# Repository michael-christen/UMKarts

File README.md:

UMKarts
=======

A repository of code for the control of rc cars that can play Mario Kart.

Steps to get it running after a clone
1) Open up the gc libero project
2) Generate Components!! This is important. Laser Tag will not work without this
3) Program the device
4) Write Application Code
5) When you are asked for your workspace, switch it to (gc\SoftConsole\gc_MSS_MSS_CM3_0\)
6) Import the projects (I don't know why you have to do this, its annoying)
	Goto File->Import
	Under General select Existing Projects into Workspace
	Under Browse goto gc\SoftConsole\gc_MSS_MSS_CM3_0
	Select all and click Finish
	* Note: You should be able to just say Browse->Ok->Finish
7) The first time you'll have to setup your Debug Configuration

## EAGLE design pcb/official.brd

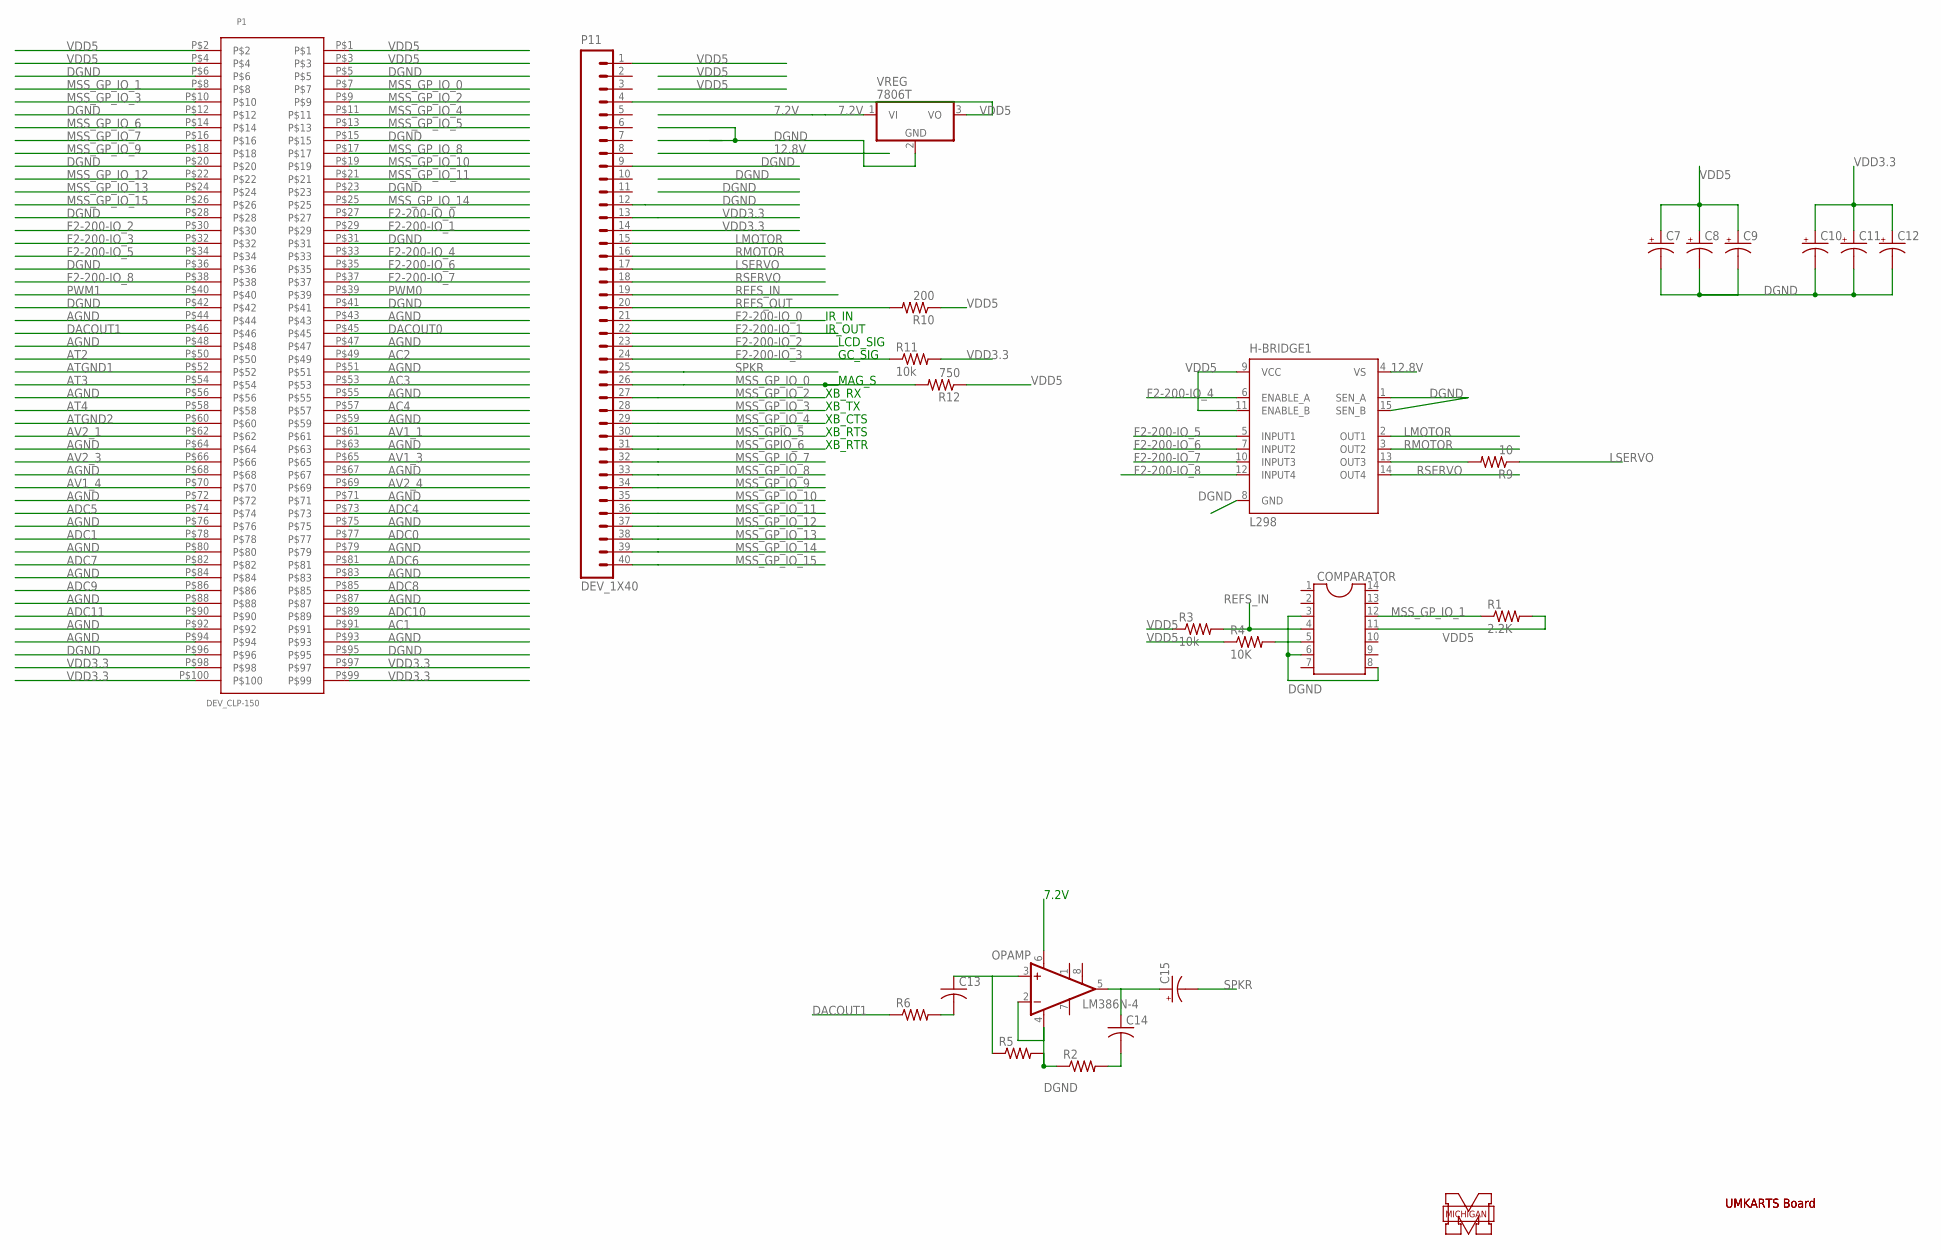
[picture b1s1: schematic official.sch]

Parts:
C7, C8, C9, C10, C11, C12, C15: CPOL-USB45181B; B45181B
C13: C-US075-032X103; C075-032X103
C14: C-US025-025X050; C025-025X050
COMPARATOR: DIL14S; SOCKET-14
H-BRIDGE1: L298; MULTIWATT-15
OPAMP: LM386N-4; DIL08
P1: DEV_CLP-150; CLP-150
P11: DEV_1X40; 1X40
R1: 2.2K; 0207/12
R2, R5, R6: R-US_0207/12; 0207/12
R3, R11: 10k; 0309/12
R4: 10K; 0309/12
R9: 10; 0309/12
R10: 200; 0309/12
R12: 750; 0309/12
VREG: 7806T; TO220H

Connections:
7.2V: P11.5, VREG.1 (VI)
12.8V: H-BRIDGE1.4 (VS), P11.8
AC1: P1.P$91
AC2: P1.P$49
AC3: P1.P$53
AC4: P1.P$57
ADC0: P1.P$77
ADC1: P1.P$78
ADC4: P1.P$73
ADC5: P1.P$74
ADC6: P1.P$81
ADC7: P1.P$82
ADC8: P1.P$85
ADC9: P1.P$86
ADC10: P1.P$89
ADC11: P1.P$90
AGND: P1.P$43, P1.P$44, P1.P$47, P1.P$48, P1.P$51, P1.P$55, P1.P$56, P1.P$59, P1.P$63, P1.P$64, P1.P$67, P1.P$68, P1.P$71, P1.P$72, P1.P$75, P1.P$76, P1.P$79, P1.P$80, P1.P$83, P1.P$84, P1.P$87, P1.P$88, P1.P$92, P1.P$93, P1.P$94
AT2: P1.P$50
AT3: P1.P$54
AT4: P1.P$58
ATGND1: P1.P$52
ATGND2: P1.P$60
AV1_1: P1.P$61
AV1_3: P1.P$65
AV1_4: P1.P$70
AV2_1: P1.P$62
AV2_3: P1.P$66
AV2_4: P1.P$69
DACOUT0: P1.P$45
DACOUT1: P1.P$46, R6.1
DGND: C7.-, C8.-, C9.-, C10.-, C11.-, C12.-, COMPARATOR.3, COMPARATOR.6, COMPARATOR.8, H-BRIDGE1.1 (SEN_A), H-BRIDGE1.8 (GND), H-BRIDGE1.15 (SEN_B), OPAMP.2 (-IN), OPAMP.4 (GND), P1.P$5, P1.P$6, P1.P$12, P1.P$15, P1.P$20, P1.P$23, P1.P$28, P1.P$31, P1.P$36, P1.P$41, P1.P$42, P1.P$95, P1.P$96, P11.6, P11.7, P11.9, P11.10, P11.11, P11.12, R2.1, R5.2, VREG.2 (GND); also elsewhere on the board
F2-200-IO_0: P1.P$27, P11.21
F2-200-IO_1: P1.P$29, P11.22
F2-200-IO_2: P1.P$30, P11.23
F2-200-IO_3: P1.P$32, P11.24, R11.1
F2-200-IO_4: H-BRIDGE1.6 (ENABLE_A), P1.P$33
F2-200-IO_5: H-BRIDGE1.5 (INPUT1), P1.P$34
F2-200-IO_6: H-BRIDGE1.7 (INPUT2), P1.P$35
F2-200-IO_7: H-BRIDGE1.10 (INPUT3), P1.P$37
F2-200-IO_8: H-BRIDGE1.12 (INPUT4), P1.P$38
LMOTOR: H-BRIDGE1.2 (OUT1), P11.15
LSERVO: P11.17, R9.1
MSS_GPIO_5: P11.30
MSS_GPIO_6: P11.31
MSS_GP_IO_0: P1.P$7, P11.26, R12.2
MSS_GP_IO_1: COMPARATOR.12, P1.P$8, R1.1
MSS_GP_IO_2: P1.P$9, P11.27
MSS_GP_IO_3: P1.P$10, P11.28
MSS_GP_IO_4: P1.P$11, P11.29
MSS_GP_IO_5: P1.P$13
MSS_GP_IO_6: P1.P$14
MSS_GP_IO_7: P1.P$16, P11.32
MSS_GP_IO_8: P1.P$17, P11.33
MSS_GP_IO_9: P1.P$18, P11.34
MSS_GP_IO_10: P1.P$19, P11.35
MSS_GP_IO_11: P1.P$21, P11.36
MSS_GP_IO_12: P1.P$22, P11.37
MSS_GP_IO_13: P1.P$24, P11.38
MSS_GP_IO_14: P1.P$25, P11.39
MSS_GP_IO_15: P1.P$26, P11.40
unnamed: H-BRIDGE1.13 (OUT3), R9.2
unnamed: C13.1, OPAMP.3 (+IN), R5.1
unnamed 63: COMPARATOR.5, R4.2; also elsewhere on the board
unnamed: C14.2, R2.2
unnamed: C14.1, C15.+, OPAMP.5 (OUT)
unnamed: C13.2, R6.2
PWM0: P1.P$39
PWM1: P1.P$40
REFS_IN: COMPARATOR.4, P11.19, R3.2
REFS_OUT: P11.20, R10.2
RMOTOR: H-BRIDGE1.3 (OUT2), P11.16
RSERVO: H-BRIDGE1.14 (OUT4), P11.18
SPKR: C15.-, P11.25
VDD3.3: C10.+, C11.+, C12.+, P1.P$97, P1.P$98, P1.P$99, P1.P$100, P11.13, P11.14, R11.2
VDD5: C7.+, C8.+, C9.+, COMPARATOR.11, H-BRIDGE1.9 (VCC), H-BRIDGE1.11 (ENABLE_B), P1.P$1, P1.P$2, P1.P$3, P1.P$4, P11.1, P11.2, P11.3, P11.4, R1.2, R3.1, R4.1, R10.1, R12.1, VREG.3 (VO)

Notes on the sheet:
MICHIGAN
7.2V
UMKARTS Board
XB_CTS
XB_RX
XB_TX
XB_RTS
XB_RTR
LCD_SIG
GC_SIG
IR_IN
IR_OUT
MAG_S

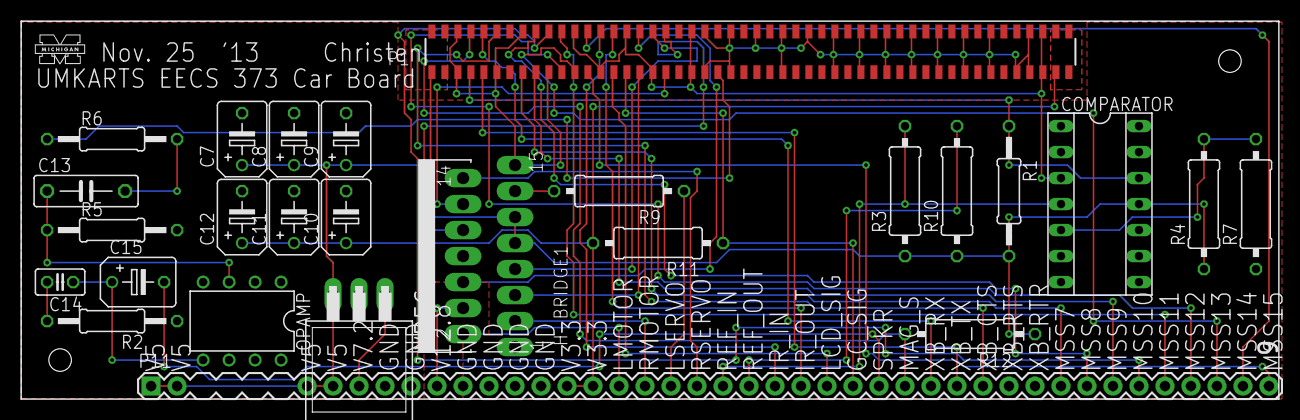
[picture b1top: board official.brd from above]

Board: 2 copper layers, 122.9 x 36.9 mm, 27 parts (0 on the bottom side), 43 nets.

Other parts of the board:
R7: 2.2k; 0309/12
U$1: UMICH

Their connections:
DGND: R7.1; also elsewhere on the board
unnamed 63: R7.2; also elsewhere on the board

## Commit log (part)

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2013-11-05 Bunch of initial files, your welcome
2013-11-05 wavebird
2013-11-06 Generalized query, and working on c lib
2013-11-07 branching gc control work
2013-11-07 Got general query working on pin J20
2013-11-12 Integrated driving
2013-11-12 Added controller files
2013-11-12 wavebirds hopefully working now, more testing needed
2013-11-12 fixed controller c code and moved back to controller.h/.c
2013-11-12 Adding intial code for our xbee driver
2013-11-12 Adding xbee receiving code. Not yet complete
2013-11-12 Added lcd interface
2013-11-14 Fixed slight bug in motor control
2013-11-14 Freed up UART1, fixed default controller data
2013-11-14 Started work on item code, NOT TESTED YET
2013-11-14 Adding UARTapb module drivers
2013-11-14 Fixed item stuff
2013-11-14 Moved variable defs out of header
2013-11-18 Adding library for circular buffer
    This library allows the instantion of a multiple producer single
    consumer buffer. This means that you can write to it in interrupts
    and there won't be any issues. We still maintain ordering.
2013-11-18 Adding .gitignore file to ignore vim .swp files
2013-11-18 Fixing bug where forgot to set item to NULL after it's been read
2013-11-18 Got item pickup working
2013-11-19 Adding xbee_writer.c class.
    xbee_writer always you to, byte by byte, generate a serial stream of
    xbee API 2 mode data from a packet in a cross platform way
2013-11-19 Changing API of circular buffer to be less confusing
    The circular buffer returned a value by passing a pointer to a
    pointer, which was just confusing to use. Now the read command
    returns a pointer to a data item to make it easier to use.
2013-11-19 Small change to hopefully prevent future bugs
2013-11-19 Adding interface files to make it easier to view which files to modify when tracking down a bug
2013-11-19 Modifying xbee_writer to make const correct
2013-11-19 Adding xbee_reader library for streaming xbee messages
    Adds the ability to read an xbee packet stream in a streaming
    fashion
2013-11-19 Adding test files for the reader/writer combination
2013-11-19 Fixing Makefile to fix clean target
2013-11-20 Adding more generic xbee functionality to interpret packets.
    Starting to add generic xbee functionality that will help in
    interpreting packets that we are getting from the xbee.
2013-11-20 Finalizing xbee_interface_rx.c and xbee_interface_tx.c so that we can send and receive data from the XBee
2013-11-20 Added original pcb file
2013-11-20 Did some more pcb stuff
2013-11-21 sound partially working
2013-11-22 Adding more packet support
2013-11-22 Actually adding files
2013-11-23 Got the listener setup, just need to add some parsing stuff
2013-11-23 Setup beginnings of parsing, going to implement on board first
2013-11-23 Possible pattern to output
2013-11-23 Slight change to main and timer
2013-11-23 Made motor interface cleaner`
2013-11-23 Fixing metadata and adding the atomics code
2013-11-23 getting the xbee code to compile by writing my own atomic funtions
2013-11-24 Added new files for sending IR
2013-11-24 Added a new APB bus intereface
2013-11-24 Added the APB_IR module
2013-11-24 Added the rest of my stuff
2013-11-24 Added all my project
2013-11-24 Updating atomic code. It now compiles, but smartfusion doesn't implment LDREX and STREX
2013-11-24 Fixed so that now its working with LED
2013-11-24 Added the laser tag for reals
2013-11-24 Added .history folders and .metadata folders to git ignore
2013-11-24 Tested the project after the new commit. It looks good
2013-11-24 And still tracking even this files
2013-11-24 Still working wth gitignore file
2013-11-24 EVEN MORE GITIGNORE FILES
2013-11-24 these files change on a synthesis, but I don't know it I can ignore them yet or not
2013-11-24 These files change on a compile
2013-11-24 updated git ignore
2013-11-24 Added sound buffer
2013-11-24 Added sound amp to pcb design file
2013-11-25 Updating atomics.h to block interrupts instead of using ldrex/strex (which are not supported by the processor)
2013-11-25 Fixing small bugs in my atomic functions, and switching over __sync_release to my own implementation of lock release
2013-11-25 This text file is for our pin assignments
2013-11-25 Slowly adding pin assignments back in
2013-11-25 Fixed pin assignment problem
2013-11-25 Re-added what was previouly ignored. This file is important
2013-11-25 Added in all the pin assignments and then open and closed the project
2013-11-25 Stop changing... MERrggg
2013-11-25 Updated main
2013-11-25 Updated the README with what to do on a new clone. Also we are back to Laser Tag working
2013-11-25 Added a laser tag wrapper to my code
2013-11-25 Added a little wrapper around the laser tag ir
2013-11-25 Good luck to whoever has to pull this shit
2013-11-25 Better pcb
2013-11-25 Rough draft
2013-11-26 Added sound samples
2013-11-26 New kyle resistor
2013-11-26 Added some sounds to items
2013-11-26 Typo whoops
2013-11-26 Different sounds for each driver
2013-11-26 Seed random item generator with real time counter
2013-11-26 Fixing small bug with atomic functions and another small bug in queue
2013-11-26 Added right resistors for comparator
2013-11-26 Edited vtimer a little more. Looking at using the RTC
2013-11-26 I moved the srand call to the rest of the initialization because using MSS_RTC_get_rtc_count disables all irqs (if only for a split second) and realy we only need to seed rand once
2013-11-26 Added some debugging keys on the controller
2013-11-26 Added the GPIO interrupt to our code
2013-11-26 Fixing bug in xbee_writer that is a copy and paste error
2013-11-26 Updating xbee_test to a better test, and modifying the interface to deal (a little) better with packet overflow
2013-11-26 Updated pins and attempt to put layers in eagle
2013-11-26 Adding xbee_interface_printf function
2013-11-26 Fixing miscalculation of maximum packet size (might actually be smaller than I expected, should look into that)
2013-11-26 Adding TODO note
2013-11-26 removing unecessary code
2013-11-26 Adding xbee_init function to the main project
2013-11-27 Some other pcb stuff
2013-11-27 Declaring as buffer here as well
2013-11-27 Fixing simple compilier warning for using the proper %s
2013-11-27 Fixing printf functionality, adding libraries to compilier, and adding some more xbee code
2013-11-27 Fixing stupid mistake
2013-11-27 Removing xp_tx_request struct, as it is no longer necessary, and correcting the max packet size to the actual size of the digimesh settings
2013-11-27 Moving some files around locally so that xbee is compatiable with all systems
2013-11-27 Got rid of delay code
2013-11-27 Fixing build
2013-11-27 Moving xbee_printf into application and out of library, also fixing main code
2013-11-27 fixing some small bugs, still trying to debug bad argument
2013-12-01 Hopefully fixing bug in listener that caused some messages not to be printed
2013-12-01 Adding type cast to make compliant with printf
2013-12-02 Working on the timer still
2013-12-03 Fixing error check on printf. We need to check if err is less than 0, not 0
2013-12-03 Starting messages protocol so that we can send messages
2013-12-03 Adding new player.c code
2013-12-03 Added star item
2013-12-03 Adding printing of address to the xbee_printf function to help with the printing
2013-12-03 Adding player code to make everything work
2013-12-03 Fixing code that broke the build. Just cleaning up small bugs in the client code
2013-12-03 Fixing WHOAMI recognition
2013-12-04 Switching to random buffer to read in dummy data
2013-12-04 Switching default player to peach
2013-12-04 Updating libero files
2013-12-04 Commiting the code for Matt that adds the driver code and fixes the self hit bug
2013-12-04 Adding documentation on the different message types
2013-12-04 Took out the FABINT handler
2013-12-04 Took out the random laser tag shoot
2013-12-04 Added a parallel array to keep track of item duration
2013-12-04 Added a player_state to try and deal with keeping track of what is going on
2013-12-04 Fixing listener to use to new code
2013-12-04 Adding simple code to game to go through simple game transition
2013-12-04 Fixing files so that it actually compiles. Making some small bug fixes
2013-12-04 Working Game Join Logic
    Our game join logic is working as of this point. This commit also
    contains a LARGE bug that would cause us to loop infinitely in the
    interrupt instead of ever exiting. But the main part of this commit
    is to allow us to do game join logic.
2013-12-05 Adding ourselves to the player table (duh), and not sending messages to ourselves
2013-12-05 Mark commiting Matt's code that he forget
2013-12-05 Added a working player_state code
2013-12-05 Updating some tx status code
2013-12-05 Adding locking functionality in interrupts so that we do not send a new packet until we receive a previous acknowledgement from the xbee
2013-12-05 messin with pwm period
2013-12-05 Added lightning slow down
2013-12-05 Removed some dead code and change the period again. Something seems to be wrong with the servos?
2013-12-05 I added a change to libero in order to make sure the motor and servo are reset with the reset command
2013-12-06 Fixing some variable names to be more conducive to the spec
2013-12-06 Removing unnecessary pound define
2013-12-06 Updating unlock functionality, so we hopefully don't fire interrupts too often
2013-12-06 Fixing frame id (actually is part of tx status response), and fixing game state transitions
2013-12-06 Not sure why these have to be changed
2013-12-06 Added a bunch of stuff from libero. Also, the sound should now stop when we get a star after 10 seconds.
2013-12-06 Rearranging code to have it all work
2013-12-06 Updating project settings that were breaking things earlier
2013-12-07 Large update to include packet status in the returned packet so that we don't have to hack a way to store it somewhere else
2013-12-07 Added code so that we would put your names on the oled
2013-12-07 Making game timeout 3 seconds instead of 2 seconds
2013-12-07 Adding code to send messages to the listener, anfixing some complier errors, and making code more readable
2013-12-07 Adding game_init to startup
2013-12-07 Added code so that you are invincible with star and after green shell hit
2013-12-07 Adding lightning functionality
2013-12-07 Fixed bug with green shell invincibility
2013-12-08 Updated lightning stuff
2013-12-08 Fixed problem with player becoming a vulenarble for a little between being hit by a green shell and becoming invincible
2013-12-08 Fixed problem with lightning and star where you were still vulnerable for a little after using both
2013-12-08 Moved the hit led code into laser_tag and also fixed lightning to turn off LED after lightning is done
2013-12-08 Removed old comments
2013-12-08 Fixed a bug with being continously invincible after a star
2013-12-08 Adding zeromq code and a simple library
2013-12-08 Adding message_types.txt to update spec
2013-12-08 Added lives and hit success sound
2013-12-08 worked on listener
2013-12-09 Better app, and fixed spelling
2013-12-09 Five hours of work, to determine one bad smartfusion. Actual changes in this commit include:
    Removing a interrupt from motor that's not needed
    Fixing small bugs (unlikely to cause problems) in xbee code
2013-12-09 Removing unnecessary include
2013-12-09 Adding main.c code to print node identifier packets
2013-12-09 Switching api to new api with drivers in packets instead of relying on addresses from xbee
2013-12-09 Fixing build errors
2013-12-09 Fixing off by one error in sending of message. Everything appears to be working now with the new message format
2013-12-09 Adding code (start + L + R) to reset the cars so they can join a new game
2013-12-09 listener looking good
2013-12-10 added die code
2013-12-10 Play two sound samples at once
2013-12-10 Adding LED init code
2013-12-10 adding gpio reset
2013-12-10 Updating item.c to not be affected to green shells from cars that are out of a game
2013-12-10 These files were modified. AKA, I have no idea what happened, but I'm pushing since the project is over
